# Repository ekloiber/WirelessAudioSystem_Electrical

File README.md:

WirelessAudioSystem_Electrical
==============================

Electrical components of the wireless audio system

Schematics (.sch) and board layouts (.brd) are editable in EAGLE CAD version 6.2 or later. 4 layer boards require non-freeware version to run.

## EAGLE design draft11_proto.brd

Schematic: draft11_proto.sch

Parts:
AVR, AVR1: LED1206; LED-1206
BATTERY: BATTERY-LIPO-JST; 1775469-2
BUTTON: TOUCH_PAD-CIRCLE-10MM; TOUCH-CIRCLE-10MM
C1, C2, C6, C11, C14, C17, C20, C29, C30, C39, C44, C46, C64, C73, C79, C81, C82, C83, C85, C86, C95, C96, C97, C100, C101, C102, C103: 100n; C0603
C3, C15, C16, C54, C62: 2.2u; C0603
C4: 100n_HF; C0603
C5: 220p_HF; C0603
C7, C10, C12, C19, C33, C35, C41, C43, C49, C51, C56, C58, C69, C75, C78: 1n; C0603
C8, C13, C76: 10p; C0603
C9: 18p; C0603
C18, C25, C28, C31, C32, C34, C40, C42, C48, C50, C52, C55, C57, C63, C65, C67, C68, C71, C72, C74, C77, C80: 1u; C0603
C21: 6.8p_HF; C0603
C22: 100p_HF; C0603
C23: 1.2p_HF; C0603
C24: 1.8p_HF; C0603
C26, C84, C87, C88, C89, C90, C91, C92, C93, C94: 10n; C0603
C36, C38, C98, C99: 470n; C0603
C45, C47, C59, C60, C61: 10u; C0603
C53, C66: 220u; C1210
C70: 10u; C0603@1
CC1: LED1206; LED-1206
CC_DEBUG: HEADER-10P-SMD-MALE2; HEADER-10P-1.27MM
CHARGE: LED1206; LED-1206
F1: 2A; 1210
GPIO: TACT_SWITCH-PTS-525; PTS-525
JTAG: HEADER-10P-SMD-MALE2; HEADER-10P-1.27MM
L1, L2: BEAD_HF; 0603
L3, L17, L19, L20, L21: BEAD; 0603
L4: 2.2n_HF; 0603
L5: 3.9n_HF; 0603
L6: 1.5n_HF; 0603
L7, L9, L10, L11, L13: 6.8n; 0603
L12: 6.8n; 0603@1
L15: BEAD; 0603@1
LED_LL: LED_RGB; PLCC-4
LED_LR: LED_RGB; PLCC-4
LED_UL: LED_RGB; PLCC-4
LED_UR: LED_RGB; PLCC-4
LINE_IN: PHONE_SW-STX-35332-5N; STX-35332-5N
NEXT: TOUCH_PAD-CIRCLE-10MM; TOUCH-CIRCLE-10MM
PHONE_OUT: PHONE_SW-STX-35332-5N; STX-35332-5N
PLAY/PAUSE: TOUCH_PAD-CIRCLE-10MM; TOUCH-CIRCLE-10MM
POWER: LED1206; LED-1206
PREV: TOUCH_PAD-CIRCLE-10MM; TOUCH-CIRCLE-10MM
Q2, Q4, Q6: 2N7002; SOT23-3
R1, R2: 4.32K; R0603
R3: 56.2K; R0603
R4, R5, R8, R12: 100; R0603
R6, R18, R37: 10K; R0603
R7, R9, R14, R21: 20K; R0603
R10, R23, R42: 220; R0603
R11: 332; R0603
R13, R16: 1M; R0603
R15, R17: 39; R0603
R19, R20, R22, R25, R28: 100K; R0603
R24, R26: 0; R0603
R27: 6.81K; R0603
R29, R30, R31, R32, R33, R34, R35, R36: 4.64K; R0603
R38: 681; R0603
R39: 4.53K; R0603
R40, R41: 1K; R0603
RESET: TACT_SWITCH-PTS-525; PTS-525
SD1: MICROSD104031-0811; MOLEX_104031-0811
SERIAL: HEADER-6X1-961106-5500; HEADER-3M-961-6P-2.54MM
SMA: SMA-REVSMA-0.62; CONREVSMA003.062
STOP: TOUCH_PAD-CIRCLE-10MM; TOUCH-CIRCLE-10MM
TO_AUX1, TO_AUX2: HEADER-10P-SMD-2MM-FEMALE; M22-63405
TO_MAIN1, TO_MAIN2: HEADER-10P-SMD-2MM-MALE; M22-53205
U1: CC2591; S-PVQFN-N16
U2: CC85XX; S-PVQFN-N40
U3: CS4270-TSSOP24; TSSOP-24L
U4: LM4881; SO08
U5: MCP1826-SOT223; SOT-223
U6: BQ2409XDGQ; S-PDSO-G10
U7: TLV700DDC; SOT-23-5
U8: SN74LVC1G80DBV; SOT-23-5
U9: CS2300-MSOP10L; MSOP-10L
U10: AT32UC3A3-LQFP-144; LQFP-144
U11: AT42QT1110-QFN-32; QFN-32
U13: SDRAM-AS4CM16S-TSSOP-54; TSSOP-54
USB: USB_MICRO_AB
VOL+: TOUCH_PAD-CIRCLE-10MM; TOUCH-CIRCLE-10MM
VOL-: TOUCH_PAD-CIRCLE-10MM; TOUCH-CIRCLE-10MM
WIRELESS: TOUCH_PAD-CIRCLE-10MM; TOUCH-CIRCLE-10MM
X2: OSCILLATOR-ASEMB; ASEMB
X3: OSCILLATOR-ASDMB; ASDMB

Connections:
12MHZ: U9.5 (CLK_IN), U10.18 (PC02), X2.3 (OUT)
!AVR_LED0: AVR.C
!AVR_LED1: AVR1.C
!CAS: U10.71 (PX41), U13.17 (!CAS)
!CHANGE: TO_AUX2.9, U10.119 (PA25)
!CS_CC8530: CC_DEBUG.5, U2.3 (!CS), U10.133 (PA07)
!CS_CLOCK: U9.8 (AD0/!CS), U10.129 (PA13)
!CS_CODEC: U3.11 (AD0/!CS), U10.115 (PA18)
!CS_SDRAM: U10.68 (PX14), U13.19 (!CS)
!CS_TOUCH: TO_AUX2.7, U10.116 (PA17)
!GPIO: GPIO.2, U10.73 (PX20)
!MUTE: U3.21 (!MUTEA), U3.24 (!MUTEB), U10.113 (PA20)
!PAIR: U2.7 (GIO1), U10.127 (PA06)
!RAS: U10.69 (PX42), U13.18 (!RAS)
!RESET: C73.1, JTAG.6, R18.1, RESET.1, U10.106 (!RESET)
!RESET_CC8530: CC_DEBUG.7, L7.2
!RESET_CODEC: U3.14 (!RESET), U10.122 (PA00)
!SD_CARD: SD1.SWA, U10.27 (PB01)
!WE_SDRAM: U10.66 (PX44), U13.16 (!WE)
A0: U10.93 (PX32), U13.23 (A0)
A1: U10.97 (PX31), U13.24 (A1)
A2: U10.96 (PX30), U13.25 (A2)
A3: U10.94 (PX29), U13.26 (A3)
A3.3V: C39.1, C70.1, L15.2, L20.2, R13.2, R16.2, U4.6 (VDD), U7.5 (VOUT)
A4: U10.91 (PX28), U13.29 (A4)
A5: U10.89 (PX27), U13.30 (A5)
A6: U10.90 (PX26), U13.31 (A6)
A7: U10.92 (PX25), U13.32 (A7)
A8: U10.86 (PX24), U13.33 (A8)
A9: U10.85 (PX23), U13.34 (A9)
A10: U10.88 (PX43), U13.22 (A10/AP)
A11: U10.80 (PX21), U13.35 (A11)
AGND: C30.2, C31.2, C39.2, C44.2, C45.2, C46.2, C47.2, C63.2, C64.2, C65.2, C70.2, C71.2, C98.2, C99.2, LINE_IN.5 (GND), PHONE_OUT.5 (GND), R19.1, R24.2, R25.1, U3.20 (AGND), U4.2 (VSS), U7.2 (GND), U10.117 (GNDANA)
ALL_GND: BATTERY.- (N), BATTERY.X1 (CASE), BATTERY.X2 (CASE), C59.2, C60.2, R24.1, R26.1, R37.1, R38.1, R39.1, U6.3 (VSS), U6.7 (ISET2), U6.GND (VSS), USB.5 (GND), USB.GND1 (GND), USB.GND2 (GND), USB.GND3 (GND), USB.GND4 (GND)
AUDIO: C53.1, R7.1, U4.7 (OUTA), U10.112 (PA24)
AUX_!CHANGE: TO_MAIN1.10, U11.28 (!CHANGE)
AUX_BLUE: R42.1, TO_MAIN2.4
AUX_CS: TO_MAIN1.8, U11.14 (!SS)
AUX_GREEN: R23.1, TO_MAIN2.6
AUX_MISO: TO_MAIN1.4, U11.16 (MISO)
AUX_MOSI: TO_MAIN1.6, U11.15 (MOSI)
AUX_RED: R10.1, TO_MAIN2.8
AUX_SCLK: TO_MAIN1.2, U11.17 (SCK)
AUX_VDD: C85.1, C86.1, R28.2, TO_MAIN1.1, TO_MAIN1.3, TO_MAIN1.5, U11.4 (VDD), U11.18 (VDD)
AUX_VDD2: LED_LL.2 (A), LED_LL.2-2 (A), LED_LR.2 (A), LED_LR.2-2 (A), LED_UL.2 (A), LED_UL.2-2 (A), LED_UR.2 (A), LED_UR.2-2 (A), TO_MAIN2.1, TO_MAIN2.2
AUX_VSS: C85.2, C86.2, TO_MAIN1.7, TO_MAIN1.9, U11.5 (VSS), U11.21 (VSS), U11.GND (VSS)
AUX_VSS1: Q2.2 (S), Q4.2 (S), Q6.2 (S), TO_MAIN2.3, TO_MAIN2.5, TO_MAIN2.7, TO_MAIN2.9, TO_MAIN2.10
AVDD: C1.1, C3.1, C4.1, C5.1, C7.1, C8.1, C9.1, C10.1, C12.1, C13.1, C14.1, C15.1, C19.1, C20.1, L1.1, L2.1, R1.2, U1.1 (AVDD_PA1), U1.10 (AVDD_PA2), U1.13 (AVDD_LNA), U1.16 (AVDD_BIAS), U2.20 (AVDD1), U2.23 (AVDD2), U2.26 (AVDD3), U2.27 (AVDD4), U2.28 (AVDD5), U2.31 (AVDD6)
AVDD_AVR: C64.1, C65.1, L20.1, U10.118 (VDDANA)
AVDD_CODEC: C30.1, C31.1, L15.1, U3.19 (VA)
BA0: U10.84 (PX18), U13.20 (BA0)
BA1: U10.83 (PX17), U13.21 (BA1)
BAT: BATTERY.+, C60.1, F1.1, R11.2, U2.29 (VBAT), U6.10 (OUT)
BCLK: L9.1, U3.4 (BCLK), U10.135 (PB07)
BLUE: TO_AUX1.7, U10.139 (PA09)
BLUE_TOP: U10.35 (PX19)
CKE: U10.74 (PX46), U13.37 (CKE)
CLK: U10.70 (PX45), U13.38 (CLK)
D0: U10.37 (PX10), U13.2 (DQ0)
D1: U10.49 (PX09), U13.4 (DQ1)
D2: U10.50 (PX08), U13.5 (DQ2)
D3: U10.54 (PX07), U13.7 (DQ3)
D3.3V: C26.1, C28.1, C29.1, C32.1, C33.1, C34.1, C35.1, C40.1, C41.1, C42.1, C43.1, C48.1, C49.1, C50.1, C51.1, C55.1, C56.1, C57.1, C58.1, C61.1, C72.1, C74.1, C75.1, C77.1, C78.1, C79.1, C80.1, C81.1, C83.1, C84.1, C95.1, C96.1, C97.1, C100.1, C101.1, C102.1, C103.1, CC_DEBUG.2, JTAG.4, L1.2, L2.2, L3.2, L17.2, L19.2, R5.2, R8.2, R12.2, R18.2, R20.2, R22.2, SD1.VDD, U3.5 (VD), U3.8 (VLC), U5.3 (VOUT), U8.5 (VCC), U9.1 (VD), U10.2 (VDDIO), U10.10 (VDDIO), U10.21 (VDDIO), U10.48 (VDDIO), U10.64 (VDDIO), U10.81 (VDDIO), U10.103 (VDDIO), U10.130 (VDDIO), U10.142 (VDDIN), U10.143 (VDDIN), U13.1 (VDD), U13.3 (VDDQ), U13.9 (VDDQ), U13.14 (VDD), U13.27 (VDD), U13.43 (VDDQ), U13.49 (VDDQ), X2.4 (VDD), X3.4 (VDD)
D4: U10.53 (PX06), U13.8 (DQ4)
D5: U10.58 (PX05), U13.10 (DQ5)
D6: U10.60 (PX04), U13.11 (DQ6)
D7: U10.63 (PX03), U13.13 (DQ7)
D8: U10.62 (PX02), U13.42 (DQ8)
D9: U10.59 (PX01), U13.44 (DQ9)
D10: U10.55 (PX00), U13.45 (DQ10)
D11: U10.52 (PX39), U13.47 (DQ11)
D12: U10.51 (PX38), U13.48 (DQ12)
D13: U10.45 (PX37), U13.50 (DQ13)
D14: U10.44 (PX36), U13.51 (DQ14)
D15: U10.38 (PX35), U13.53 (DQ15)
D+_UC: R15.2, U10.6 (D+_HS), USB.3 (D+)
D-_UC: R17.2, U10.5 (D-_HS), USB.2 (D-)
DGND: C1.2, C2.2, C3.2, C4.2, C5.2, C6.2, C7.2, C8.2, C9.2, C10.2, C11.2, C12.2, C13.2, C14.2, C15.2, C16.2, C17.2, C18.2, C19.2, C20.2, C23.2, C24.2, C25.2, C26.2, C28.2, C29.2, C32.2, C33.2, C34.2, C35.2, C40.2, C41.2, C42.2, C43.2, C48.2, C49.2, C50.2, C51.2, C54.2, C55.2, C56.2, C57.2, C58.2, C61.2, C62.2, C68.2, C69.2, C72.2, C73.2, C74.2, C75.2, C76.2, C77.2, C78.2, C79.2, C80.2, C81.2, C82.2, C83.2, C84.2, C95.2, C96.2, C97.2, C100.2, C101.2, C102.2, C103.2, CC_DEBUG.1, GPIO.4, JTAG.2, JTAG.10, L6.1, POWER.C, R2.1, R3.1, R6.1, R26.2, R27.1, RESET.3, SD1.GND1 (GND), SD1.GND2 (GND), SD1.GND3 (GND), SD1.GND4 (GND), SD1.SWB, SD1.VSS (GND), SERIAL.6, SMA.GND1 (GND), SMA.GND2 (GND), SMA.GND3 (GND), SMA.GND4 (GND), TO_AUX1.4, TO_AUX1.6, TO_AUX1.8, TO_AUX1.9, TO_AUX1.10, TO_AUX2.6, TO_AUX2.8, TO_AUX2.10, U1.8 (GND), U1.9 (GND), U1.12 (GND), U1.14 (GND), U1.GND, U2.19 (AD2/GIO9), U2.32 (SCL/GIO10), U2.33 (SDA/GIO11), U2.34 (GIO12), U2.35 (GIO13), U2.GND, U3.6 (DGND), U5.2 (GND), U5.4 (GND), U8.3 (GND), U9.2 (GND), U9.7 (FILTN), U10.4 (GNDIO), U10.7 (GNDIO), U10.20 (GNDIO), U10.47 (GNDIO), U10.65 (GNDIO), U10.82 (GNDIO), U10.102 (GNDIO), U10.131 (GNDIO), U10.140 (GNDCORE), U10.144 (GNDPLL), U13.6 (VSSQ), U13.12 (VSSQ), U13.28 (VSS), U13.41 (VSS), U13.46 (VSSQ), U13.52 (VSSQ), U13.54 (VSS), X2.1 (!EN), X2.2 (VSS), X3.1 (!EN), X3.2 (VSS)
DIN: L13.1, U3.1 (DIN), U10.11 (PB08)
DOUT: L11.1, U3.7 (DOUT), U10.17 (PB09)
GREEN: TO_AUX1.5, U10.134 (PB06)
IN_L: C38.1, LINE_IN.4 (L), R19.2
IN_R: C36.1, LINE_IN.1 (R)
IOVDD: C2.1, C6.1, C11.1, C16.1, C17.1, C18.1, CC1.A, L3.1, U2.10 (IOVDD1), U2.12 (IOVDD2), U2.18 (IOVDD3), U2.37 (IOVDD4), U2.40 (DVDD)
LDQM: U10.61 (PX34), U13.15 (LDQM)
LINEIN_SENSE: LINE_IN.3 (L_SW), R13.1, U10.109 (PA21)
LNA_EN: U1.6 (EN), U2.38 (XLNAEN)
MCI-CLK: SD1.CLK (CLK/SCLK), U10.26 (PA27)
MCI-CMD: R22.1, SD1.CMD (CMD/MOSI), U10.28 (PA28)
MCI-DATA0: R20.1, SD1.DAT0 (DAT0/MISO), U10.23 (PA29)
MCI-DATA1: SD1.DAT1 (DAT1/NC), U10.14 (PA30)
MCI-DATA2: SD1.DAT2 (DAT2/NC), U10.29 (PA31)
MCI-DATA3: SD1.CD/DAT3 (CD/DAT3/!CS), U10.30 (PB00)
MCLK: U3.3 (MCLK), U8.2 (CLK), U9.3 (CLK_OUT)
MISO0: CC_DEBUG.10, U2.6 (MISO), U10.136 (PA11)
MISO1: TO_AUX2.3, U3.9 (SDA/MISO), U10.114 (PA19)
MOSI0: CC_DEBUG.8, U2.5 (MOSI), U9.10 (SDA/MOSI), U10.138 (PA10)
MOSI1: TO_AUX2.5, U3.12 (AD1/MOSI), U10.128 (PA16)
unnamed: U2.21 (X1), X3.3 (OUT)
unnamed: Q2.1 (G), R10.2
unnamed: L7.1, U2.11 (!RESET)
unnamed: L11.2, U2.16 (AD0/GIO7)
unnamed: L9.2, U2.14 (BCLK/GIO5)
unnamed: C94.2, R36.1, U11.22 (SNS7K/DETECT0)
unnamed: R2.2, U1.15 (BIAS)
unnamed: R1.1, U1.7 (HGM)
unnamed: C22.2, SMA.SIG
unnamed: AVR1.A, R5.1
unnamed: PLAY/PAUSE.P$1, R36.2
unnamed: AVR.A, R8.1
unnamed: L4.1, U1.11 (ANT)
unnamed: C23.1, L4.2, L5.1
unnamed: C21.1, L5.2
unnamed: C21.2, C22.1, C24.1, L6.2
unnamed: C94.1, U11.23 (SNS7/DETECT1)
unnamed: L12.1, U2.36 (XPAEN)
unnamed: R3.2, U2.30 (RBIAS)
unnamed: C52.2, C98.1, R9.2
unnamed: C25.1, U2.39 (DCPL)
unnamed: C71.1, L21.1, U7.1 (VIN), U7.3 (EN)
unnamed: Q4.1 (G), R23.2
unnamed: C67.2, C99.1, R14.2
unnamed: L10.2, U2.15 (WCLK/GIO6)
unnamed: C63.1, U4.1 (BYPASS)
unnamed: L13.2, U2.17 (AD1/GIO8)
unnamed: R4.1, U2.9 (GIO3)
unnamed: CC1.C, R4.2
unnamed: C90.2, R32.1, U11.9 (SNS3K)
unnamed: POWER.A, R12.1
unnamed: CHARGE.C, U6.8 (!CHG)
unnamed: CHARGE.A, R11.1
unnamed: C68.1, C69.1, U10.141 (VDDCORE)
unnamed: Q6.1 (G), R42.2
unnamed: R17.1, U10.8 (D-_FS)
unnamed: C66.1, R21.1, U4.5 (OUTB)
unnamed: C91.2, R33.1, U11.11 (SNS4K)
unnamed: C92.2, R34.1, U11.13 (SNS5K)
unnamed: C87.2, R29.1, U11.1 (SNS0K)
unnamed: R38.2, U6.2 (ISET)
unnamed: C88.2, R30.1, U11.3 (SNS1K)
unnamed: R15.1, U10.9 (D+_FS)
unnamed: C76.1, R27.2, U10.3 (USB_VBIAS)
unnamed: C67.1, R40.1
unnamed: F1.2, L21.2, U5.1 (VIN)
unnamed: C52.1, R41.1
unnamed: R7.2, R9.1, U4.8 (INA)
unnamed: R14.1, R21.2, U4.4 (INB)
unnamed: LED_LL.1 (KR), LED_LL.1-2 (KR), LED_LR.1 (KR), LED_LR.1-2 (KR), LED_UL.1 (KR), LED_UL.1-2 (KR), LED_UR.1 (KR), LED_UR.1-2 (KR), Q2.3 (D)
unnamed: LED_LL.4 (KG), LED_LL.4-2 (KG), LED_LR.4 (KG), LED_LR.4-2 (KG), LED_UL.4 (KG), LED_UL.4-2 (KG), LED_UR.4 (KG), LED_UR.4-2 (KG), Q4.3 (D)
unnamed: C87.1, U11.32 (SNS0)
unnamed: C90.1, U11.8 (SNS3)
unnamed: R32.2, VOL+.P$1
unnamed: C91.1, U11.10 (SNS4)
unnamed: R33.2, WIRELESS.P$1
unnamed: C92.1, U11.12 (SNS5)
unnamed: R34.2, VOL-.P$1
unnamed: R37.2, U6.9 (TS)
unnamed: C54.1, L17.1, TO_AUX1.1, TO_AUX1.2
unnamed: R39.2, U6.4 (PRETERM)
unnamed: C93.2, R35.1, U11.19 (SNS6K)
unnamed: PREV.P$1, R35.2
unnamed: C93.1, U11.20 (SNS6)
unnamed: R28.1, U11.29 (!RESET)
unnamed: LED_LL.3 (KB), LED_LL.3-2 (KB), LED_LR.3 (KB), LED_LR.3-2 (KB), LED_UL.3 (KB), LED_UL.3-2 (KB), LED_UR.3 (KB), LED_UR.3-2 (KB), Q6.3 (D)
unnamed: C62.1, L19.1, TO_AUX2.2, TO_AUX2.4
unnamed: R29.2, STOP.P$1
unnamed: C88.1, U11.2 (SNS1)
unnamed: NEXT.P$1, R30.2
unnamed: C46.1, C47.1, U3.17 (VQ)
unnamed: C44.1, C45.1, U3.18 (FILT+)
unnamed: C89.2, R31.1, U11.6 (SNS2K)
unnamed: C36.2, U3.15 (AINA)
unnamed: C38.2, U3.16 (AINB)
unnamed: C89.1, U11.7 (SNS2)
unnamed: C82.1, U9.6 (FILTP)
unnamed: BUTTON.P$1, R31.2
OUT_L: R41.2, U3.23 (OUTB)
OUT_R: R40.2, U3.22 (OUTA)
PA_EN: L12.2, R6.2, U1.5 (PAEN)
PHONE_L: C53.2, PHONE_OUT.4 (L), R25.2
PHONE_R: C66.2, PHONE_OUT.1 (R)
PHONE_SENSE: PHONE_OUT.3 (L_SW), R16.1, U10.110 (PA22)
RED: TO_AUX1.3, U10.132 (PA12)
RF_N: U1.2 (RF_N), U2.25 (RF_N)
RF_P: U1.4 (RF_P), U2.24 (RF_P)
RXD: SERIAL.3, U10.125 (PA03)
SCLK0: CC_DEBUG.6, U2.4 (SCLK), U9.9 (SCL/SCLK), U10.137 (PA08)
SCLK1: TO_AUX2.1, U3.10 (SCL/SCLK), U10.101 (PA15)
SHDN: U4.3 (SHUTDOWN), U10.111 (PA23)
TCK: JTAG.1, U10.107 (TCK)
TDI: JTAG.9, U10.108 (TDI)
TDO: JTAG.3, U10.105 (TDO)
TMS: JTAG.5, U10.104 (TMS)
TXD: SERIAL.2, U10.126 (PA04)
UC_MCLK: U8.1 (D), U8.4 (!Q), U10.13 (PC04)
UDQM: U10.67 (PX11), U13.39 (UDQM)
USBOTGID: U10.121 (PB05), USB.4 (ID)
VBUS: C59.1, U6.1 (IN), U10.1 (USB_VBUS), USB.1 (VBUS)
WCLK: L10.1, U3.2 (WCLK), U10.31 (PB11)

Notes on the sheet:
See Note
AVDD_PA1 1.85mm
AVDD_PA2 2.40mm
AVDD_LNA 6.90mm
Trace length at w=0.254mm
Audio
Power
Control
AVDD traces act as transmission lines
Lowest value cap should be placed closest to pin
Parts with '_HF' should be rated to >2.4GHz
Wireless SoC
LNA/PA
Ensure pull-up on !SD_CARD
MCLK is either: 24.576MHz (n*48kHz) 22.5792MHz (n*44.1kHz)
UC_MCLK is either: 12.288MHz (n*48kHz) 11.2896MHz (n*44.1kHz)

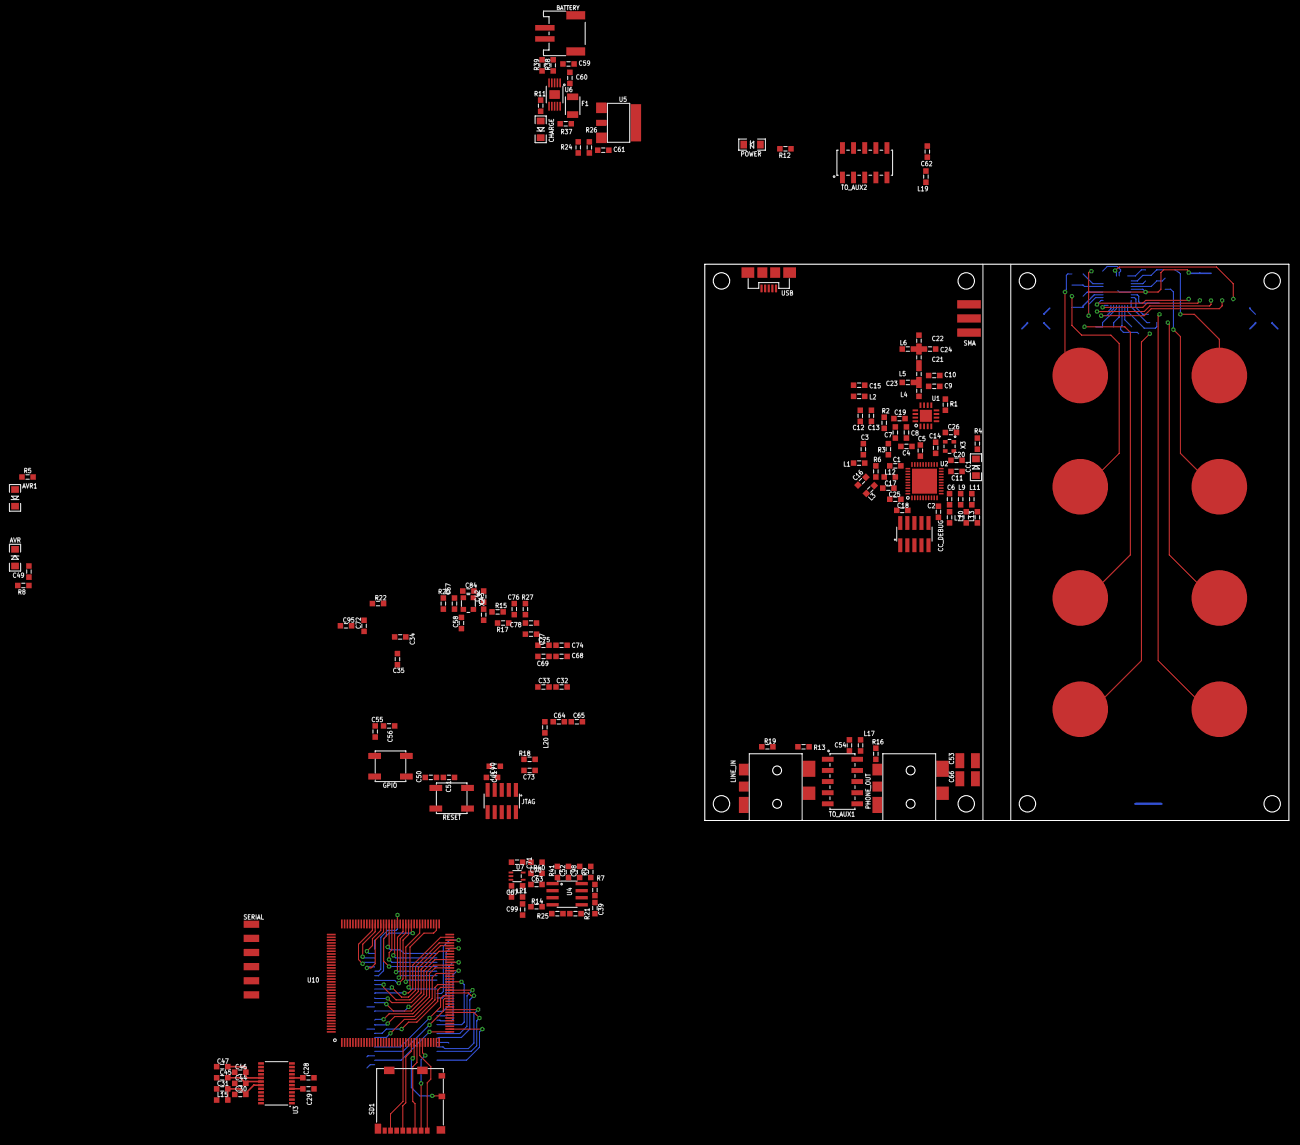
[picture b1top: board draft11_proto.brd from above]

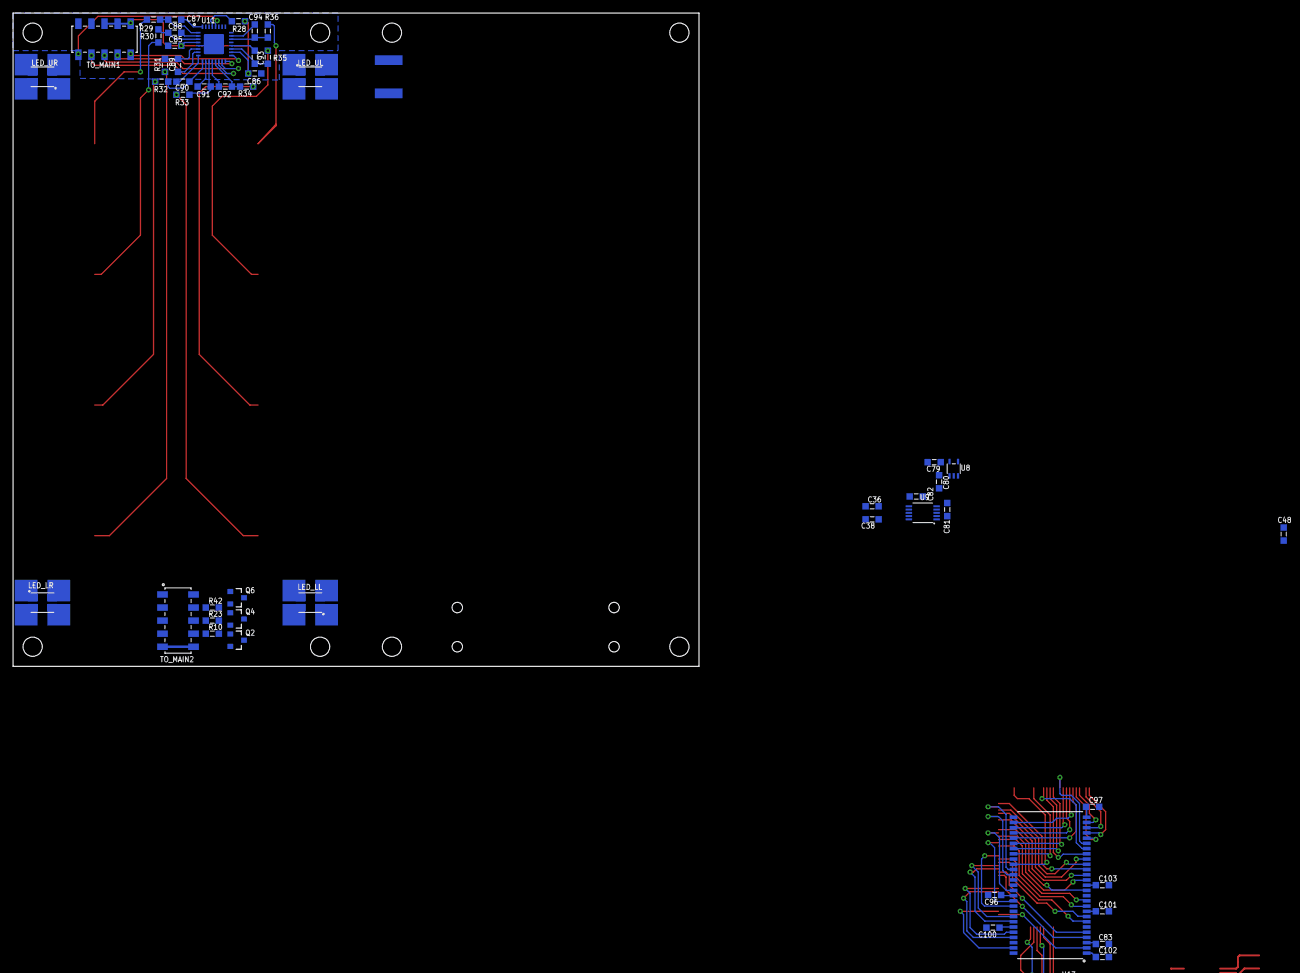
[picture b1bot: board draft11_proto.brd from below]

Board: 4 copper layers, 105.0 x 100.0 mm, 219 parts (49 on the bottom side), 196 nets.

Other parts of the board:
U$1, U$2, U$3, U$4, U$6, U$7, U$8, U$9: STANDOFF_3/16
U$5: UBBP01

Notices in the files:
parts and their libraries:
SparkFun-LED: Licensing: CC v3.0 Share-Alike You are welcome to use this library for commercial purposes.
